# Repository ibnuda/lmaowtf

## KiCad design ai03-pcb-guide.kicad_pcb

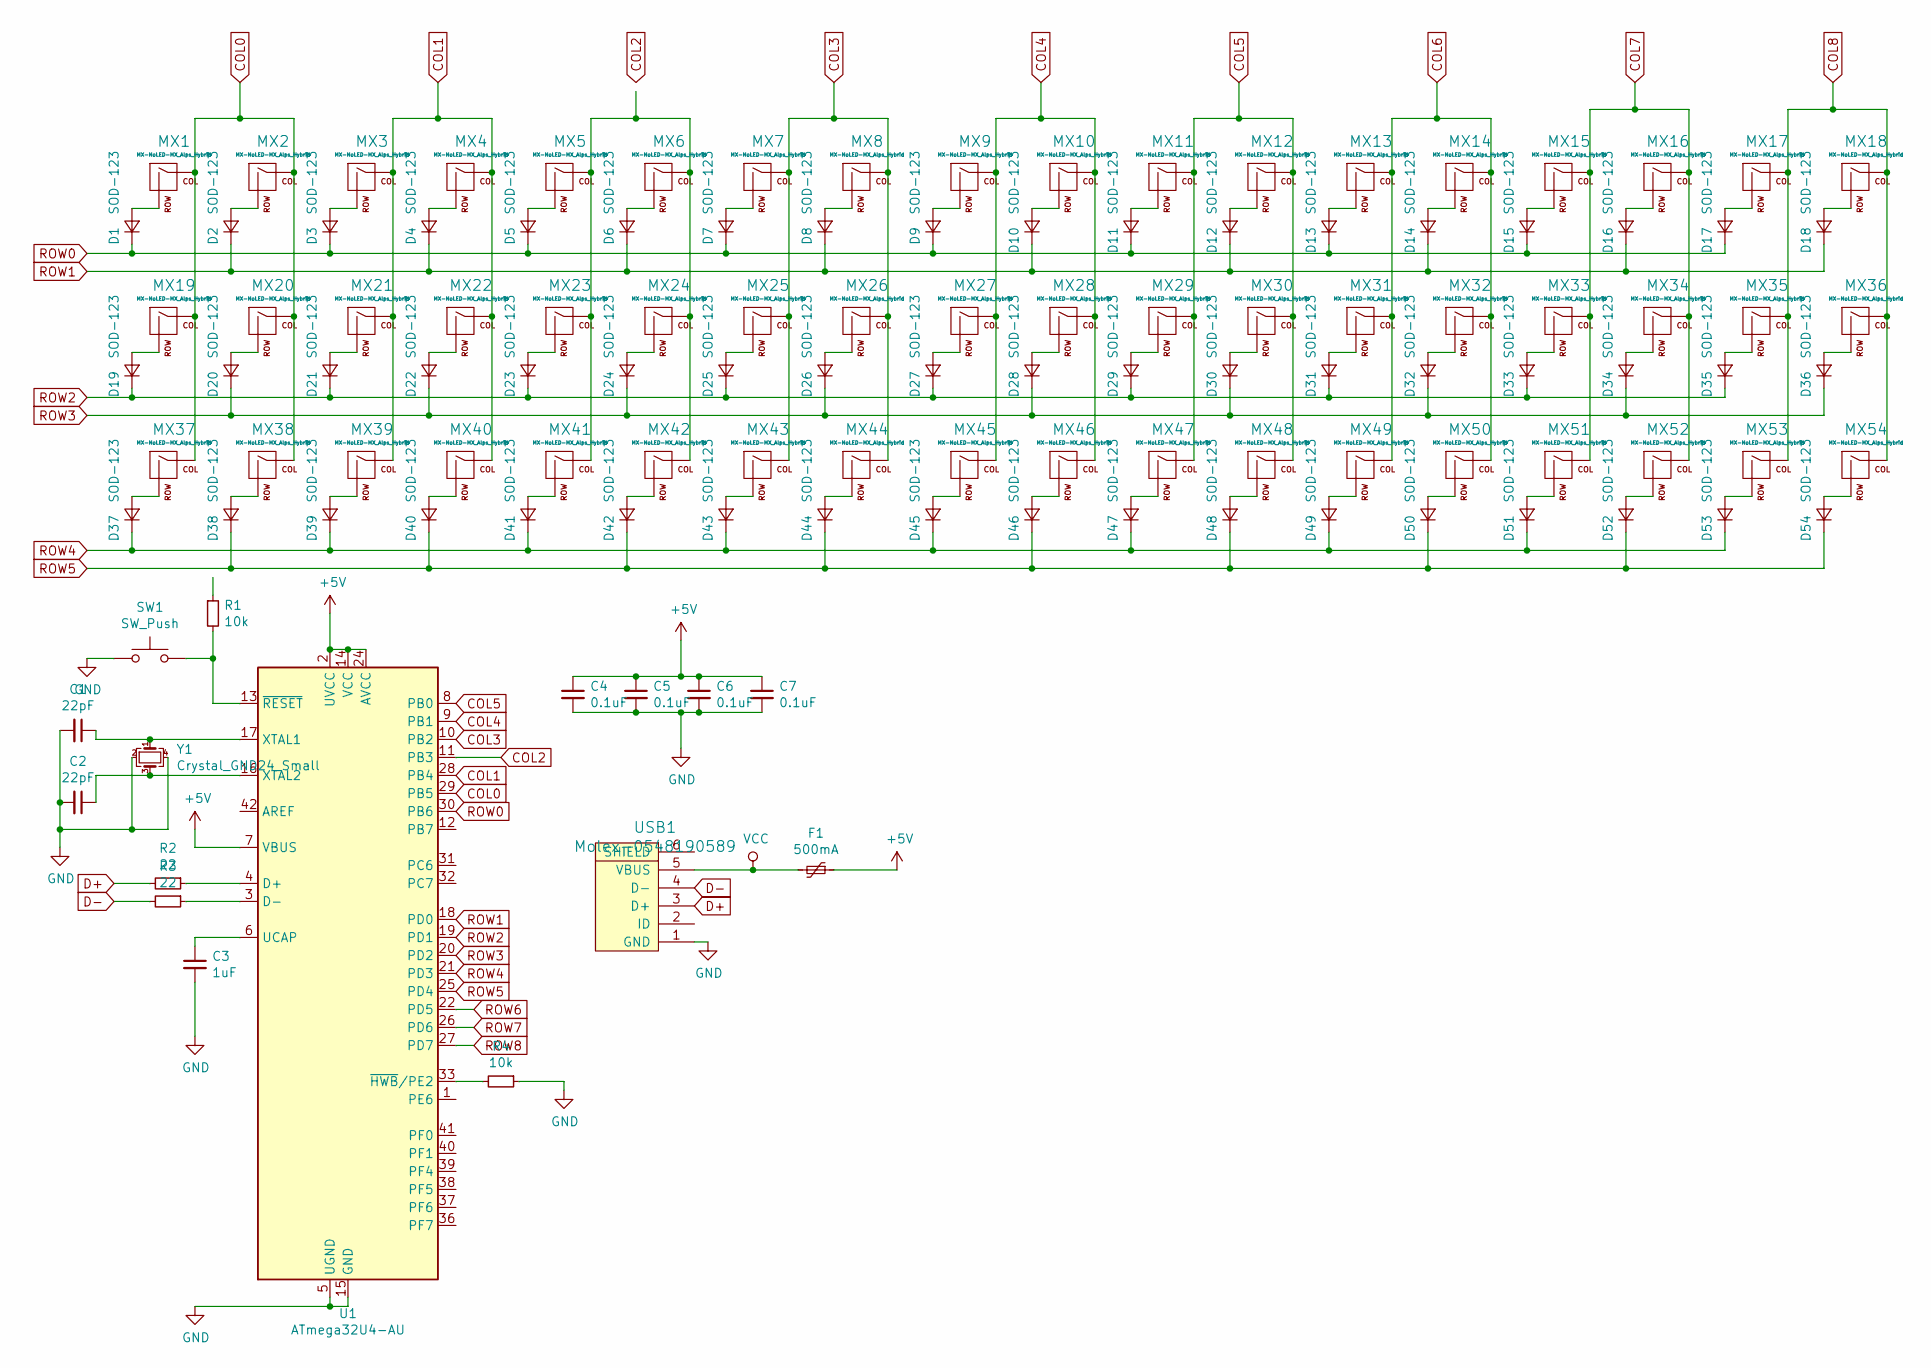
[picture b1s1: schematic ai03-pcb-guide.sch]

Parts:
C1, C2: 22pF; C_0805_2012Metric
C3: 1uF; C_0805_2012Metric
C4, C5, C6, C7: 0.1uF; C_0805_2012Metric
D1, D2, D3, D4, D5, D6, D7, D8, D9, D10, D11, D12, D13, D14, D15, D16, D17, D18, D19, D20, D21, D22, D23, D24, D25, D26, D27, D28, D29, D30, D31, D32, D33, D34, D35, D36, D37, D38, D39, D40, D41, D42, D43, D44, D45, D46, D47, D48, D49, D50, D51, D52, D53, D54: SOD-123; D_SOD-123-Pretty
F1: 500mA; Fuse_SMD1206_Reflow
MX1, MX2, MX3, MX4, MX5, MX6, MX7, MX8, MX9, MX10, MX11, MX12, MX13, MX14, MX15, MX16, MX17, MX18, MX19, MX20, MX21, MX22, MX23, MX24, MX25, MX26, MX27, MX28, MX29, MX30, MX31, MX32, MX33, MX34, MX35, MX36, MX37, MX38, MX39, MX40, MX41, MX42, MX43, MX44, MX45, MX46, MX47, MX48, MX49, MX50, MX51, MX52, MX53, MX54: MX-NoLED-MX_Alps_Hybrid; MX-Alps-Choc-X-1U-NoLED
R1, R4: 10k; R_0805_2012Metric
R2, R3: 22; R_0805_2012Metric
SW1: SW_Push
U1: ATmega32U4-AU; TQFP-44_10x10mm_P0.8mm
USB1: Molex-0548190589
Y1: Crystal_GND24_Small; Crystal_SMD_3225-4Pin_3.2x2.5mm

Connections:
+5V: C4.1, C5.1, C6.1, C7.1, F1.1, U1.2 (UVCC), U1.7 (VBUS), U1.14 (VCC), U1.24 (AVCC), U1.34 (VCC), U1.44 (AVCC)
COL0: MX1.1 (COL), MX2.1 (COL), MX19.1 (COL), MX20.1 (COL), MX37.1 (COL), MX38.1 (COL), U1.29 (PB5)
COL1: MX3.1 (COL), MX4.1 (COL), MX21.1 (COL), MX22.1 (COL), MX39.1 (COL), MX40.1 (COL), U1.28 (PB4)
COL2: U1.11 (PB3)
COL3: MX7.1 (COL), MX8.1 (COL), MX25.1 (COL), MX26.1 (COL), MX43.1 (COL), MX44.1 (COL), U1.10 (PB2)
COL4: MX9.1 (COL), MX10.1 (COL), MX27.1 (COL), MX28.1 (COL), MX45.1 (COL), MX46.1 (COL), U1.9 (PB1)
COL5: MX11.1 (COL), MX12.1 (COL), MX29.1 (COL), MX30.1 (COL), MX47.1 (COL), MX48.1 (COL), U1.8 (PB0)
COL6: MX13.1 (COL), MX14.1 (COL), MX31.1 (COL), MX32.1 (COL), MX49.1 (COL), MX50.1 (COL)
COL7: MX15.1 (COL), MX16.1 (COL), MX33.1 (COL), MX34.1 (COL), MX51.1 (COL), MX52.1 (COL)
COL8: MX17.1 (COL), MX18.1 (COL), MX35.1 (COL), MX36.1 (COL), MX53.1 (COL), MX54.1 (COL)
D+: R2.2, USB1.3 (D+)
D-: R3.2, USB1.4 (D-)
GND: C1.2, C2.2, C3.2, C4.2, C5.2, C6.2, C7.2, R4.1, SW1.1, U1.5 (UGND), U1.15 (GND), U1.23 (GND), U1.35 (GND), U1.43 (GND), USB1.1 (GND), Y1.2, Y1.4
unnamed: C1.1, U1.17 (XTAL1), Y1.1
unnamed: C2.1, U1.16 (XTAL2), Y1.3
unnamed: C3.1, U1.6 (UCAP)
unnamed: D1.2 (A), MX1.2 (ROW)
unnamed: D2.2 (A), MX2.2 (ROW)
unnamed: D3.2 (A), MX3.2 (ROW)
unnamed: D4.2 (A), MX4.2 (ROW)
unnamed: D5.2 (A), MX5.2 (ROW)
unnamed: D6.2 (A), MX6.2 (ROW)
unnamed: D7.2 (A), MX7.2 (ROW)
unnamed: D8.2 (A), MX8.2 (ROW)
unnamed: D9.2 (A), MX9.2 (ROW)
unnamed: D10.2 (A), MX10.2 (ROW)
unnamed: D11.2 (A), MX11.2 (ROW)
unnamed: D12.2 (A), MX12.2 (ROW)
unnamed: D13.2 (A), MX13.2 (ROW)
unnamed: D14.2 (A), MX14.2 (ROW)
unnamed: D15.2 (A), MX15.2 (ROW)
unnamed: D16.2 (A), MX16.2 (ROW)
unnamed: D17.2 (A), MX17.2 (ROW)
unnamed: D18.2 (A), MX18.2 (ROW)
unnamed: D19.2 (A), MX19.2 (ROW)
unnamed: D20.2 (A), MX20.2 (ROW)
unnamed: D21.2 (A), MX21.2 (ROW)
unnamed: D22.2 (A), MX22.2 (ROW)
unnamed: D23.2 (A), MX23.2 (ROW)
unnamed: D24.2 (A), MX24.2 (ROW)
unnamed: D25.2 (A), MX25.2 (ROW)
unnamed: D26.2 (A), MX26.2 (ROW)
unnamed: D27.2 (A), MX27.2 (ROW)
unnamed: D28.2 (A), MX28.2 (ROW)
unnamed: D29.2 (A), MX29.2 (ROW)
unnamed: D30.2 (A), MX30.2 (ROW)
unnamed: D31.2 (A), MX31.2 (ROW)
unnamed: D32.2 (A), MX32.2 (ROW)
unnamed: D33.2 (A), MX33.2 (ROW)
unnamed: D34.2 (A), MX34.2 (ROW)
unnamed: D35.2 (A), MX35.2 (ROW)
unnamed: D36.2 (A), MX36.2 (ROW)
unnamed: D37.2 (A), MX37.2 (ROW)
unnamed: D38.2 (A), MX38.2 (ROW)
unnamed: D39.2 (A), MX39.2 (ROW)
unnamed: D40.2 (A), MX40.2 (ROW)
unnamed: D41.2 (A), MX41.2 (ROW)
unnamed: D42.2 (A), MX42.2 (ROW)
unnamed: D43.2 (A), MX43.2 (ROW)
unnamed: D44.2 (A), MX44.2 (ROW)
unnamed: D45.2 (A), MX45.2 (ROW)
unnamed: D46.2 (A), MX46.2 (ROW)
unnamed: D47.2 (A), MX47.2 (ROW)
unnamed: D48.2 (A), MX48.2 (ROW)
unnamed: D49.2 (A), MX49.2 (ROW)
unnamed: D50.2 (A), MX50.2 (ROW)
unnamed: D51.2 (A), MX51.2 (ROW)
unnamed: D52.2 (A), MX52.2 (ROW)
unnamed: D53.2 (A), MX53.2 (ROW)
unnamed: D54.2 (A), MX54.2 (ROW)
unnamed: MX5.1 (COL), MX6.1 (COL), MX23.1 (COL), MX24.1 (COL), MX41.1 (COL), MX42.1 (COL)
unnamed: R1.2, SW1.2, U1.13 (~RESET)
unnamed: R2.1, U1.4 (D+)
unnamed: R3.1, U1.3 (D-)
unnamed: R4.2, U1.33 (~HWB~/PE2)
ROW0: D1.1 (K), D3.1 (K), D5.1 (K), D7.1 (K), D9.1 (K), D11.1 (K), D13.1 (K), D15.1 (K), D17.1 (K), U1.30 (PB6)
ROW1: D2.1 (K), D4.1 (K), D6.1 (K), D8.1 (K), D10.1 (K), D12.1 (K), D14.1 (K), D16.1 (K), D18.1 (K), U1.18 (PD0)
ROW2: D19.1 (K), D21.1 (K), D23.1 (K), D25.1 (K), D27.1 (K), D29.1 (K), D31.1 (K), D33.1 (K), D35.1 (K), U1.19 (PD1)
ROW3: D20.1 (K), D22.1 (K), D24.1 (K), D26.1 (K), D28.1 (K), D30.1 (K), D32.1 (K), D34.1 (K), D36.1 (K), U1.20 (PD2)
ROW4: D37.1 (K), D39.1 (K), D41.1 (K), D43.1 (K), D45.1 (K), D47.1 (K), D49.1 (K), D51.1 (K), D53.1 (K), U1.21 (PD3)
ROW5: D38.1 (K), D40.1 (K), D42.1 (K), D44.1 (K), D46.1 (K), D48.1 (K), D50.1 (K), D52.1 (K), D54.1 (K), U1.25 (PD4)
ROW6: U1.22 (PD5)
ROW7: U1.26 (PD6)
ROW8: U1.27 (PD7)
VCC: F1.2, USB1.5 (VBUS)

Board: 2 copper layers, 122 parts (0 on the bottom side), 80 nets, no tracks yet.

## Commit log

2019-06-12 lmao wtf
